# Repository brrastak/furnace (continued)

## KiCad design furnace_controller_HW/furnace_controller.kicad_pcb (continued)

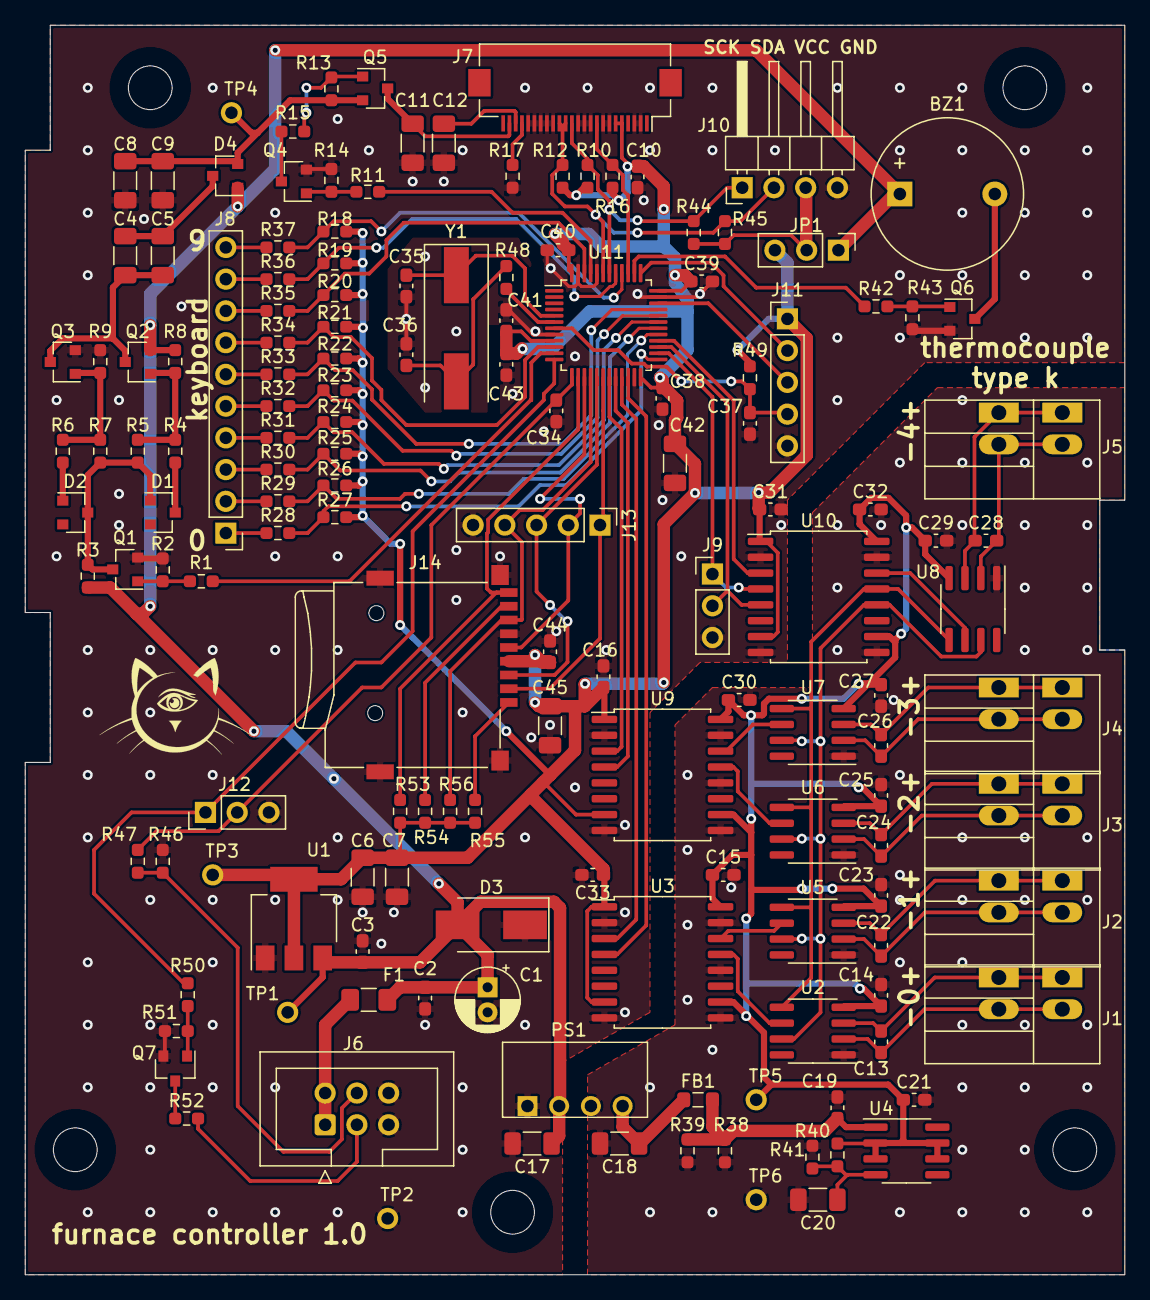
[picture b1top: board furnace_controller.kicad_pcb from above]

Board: 2 copper layers, 88.0 x 100.0 mm, 155 parts (0 on the bottom side), 96 nets.

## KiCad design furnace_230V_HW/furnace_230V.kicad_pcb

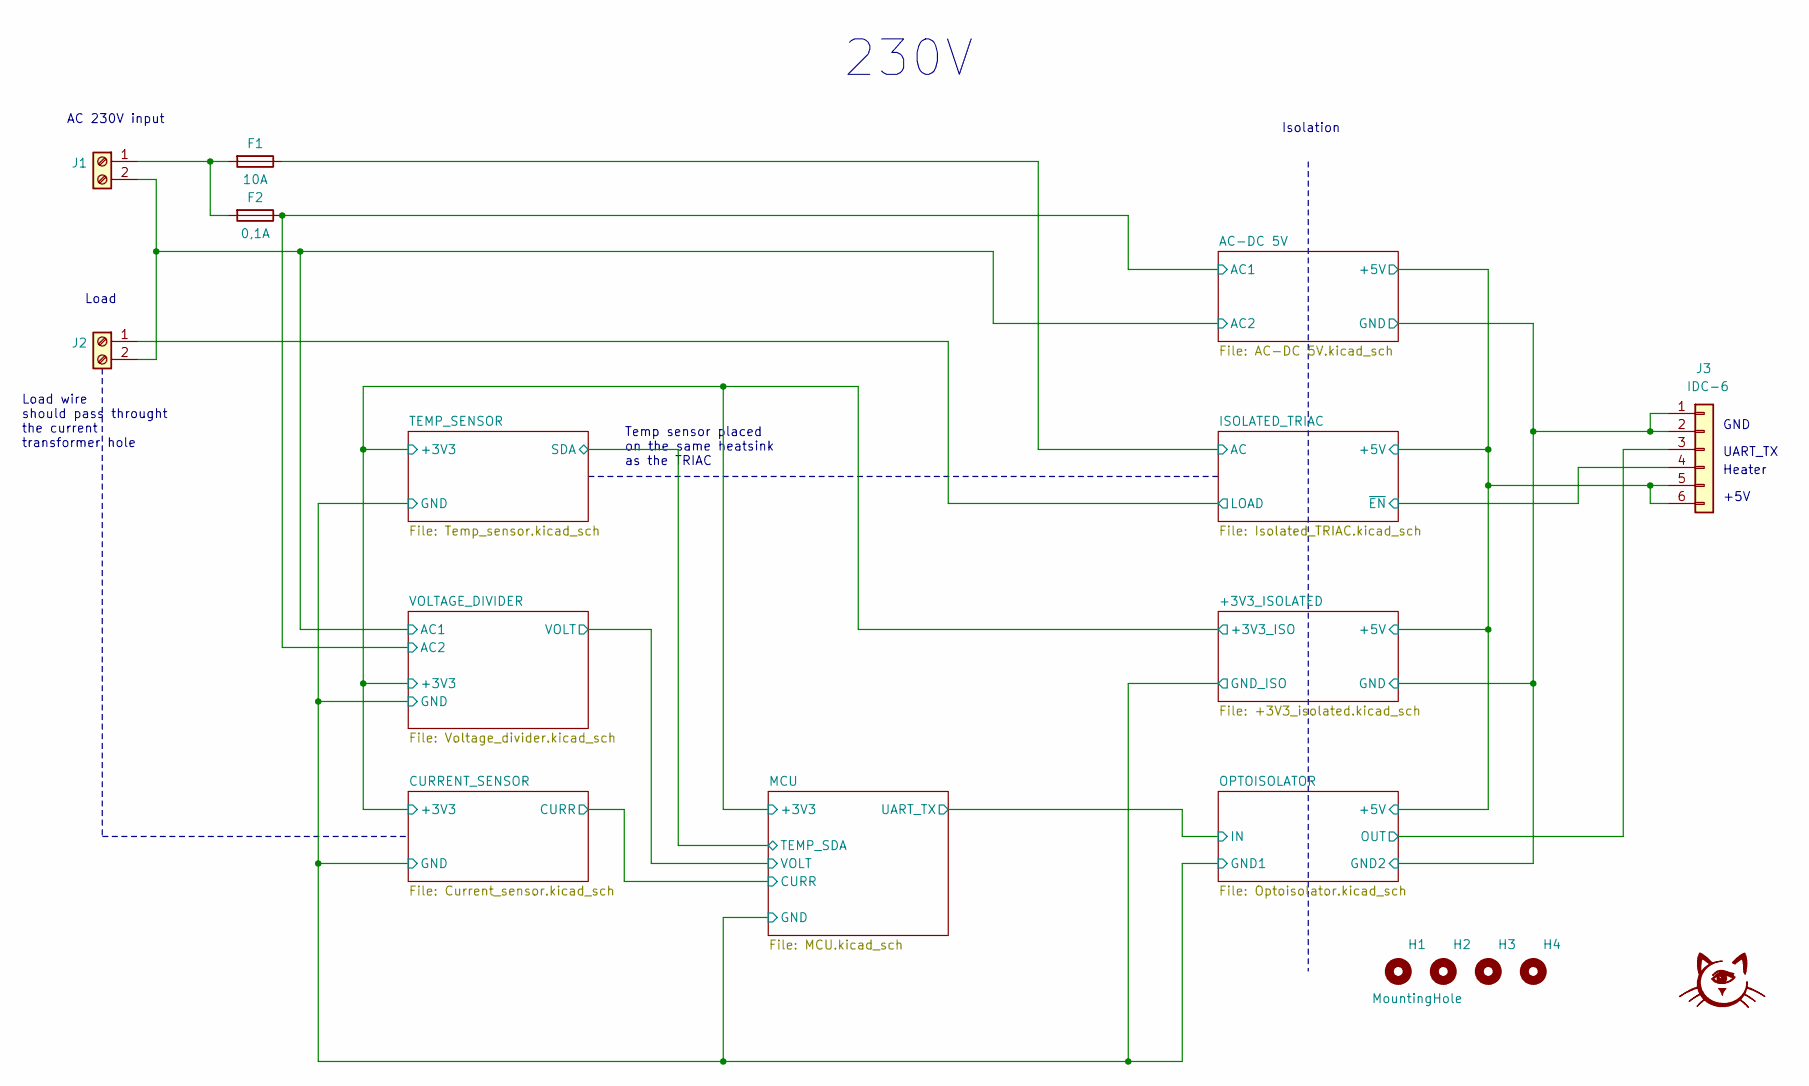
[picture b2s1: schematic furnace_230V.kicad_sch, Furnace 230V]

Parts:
F1: 10A; Fuseholder_Cylinder-5x20mm_Stelvio-Kontek_PTF78_Horizontal_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
F2: 0,1A; Fuseholder_Cylinder-5x20mm_Stelvio-Kontek_PTF78_Horizontal_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
G1: LOGO; stamp
H1, H2, H3, H4: MountingHole; hole_D3.5mm
J1, J2: KF7.62-2P
J3: IDC-6; IDC-Header_2x03_P2.54mm_Vertical

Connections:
/+3V3_ISOLATED/+5V: J3.5, J3.6; also elsewhere on the board
/+3V3_ISOLATED/GND: J3.1, J3.2; also elsewhere on the board
/AC-DC 5V/AC1: F2.1; also elsewhere on the board
/ISOLATED_TRIAC/AC: F1.1; also elsewhere on the board
/ISOLATED_TRIAC/LOAD: J2.1; also elsewhere on the board
/ISOLATED_TRIAC/~EN: J3.4; also elsewhere on the board
/OPTOISOLATOR/OUT: J3.3; also elsewhere on the board
/VOLTAGE_DIVIDER/AC1: J1.2, J2.2; also elsewhere on the board
unnamed: F1.2, F2.2, J1.1

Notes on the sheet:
GND
Isolation
230V
Load wire should pass throught the current transformer hole
AC 230V input
UART_TX
Load
Heater
Temp sensor placed on the same heatsink as the TRIAC
+5V

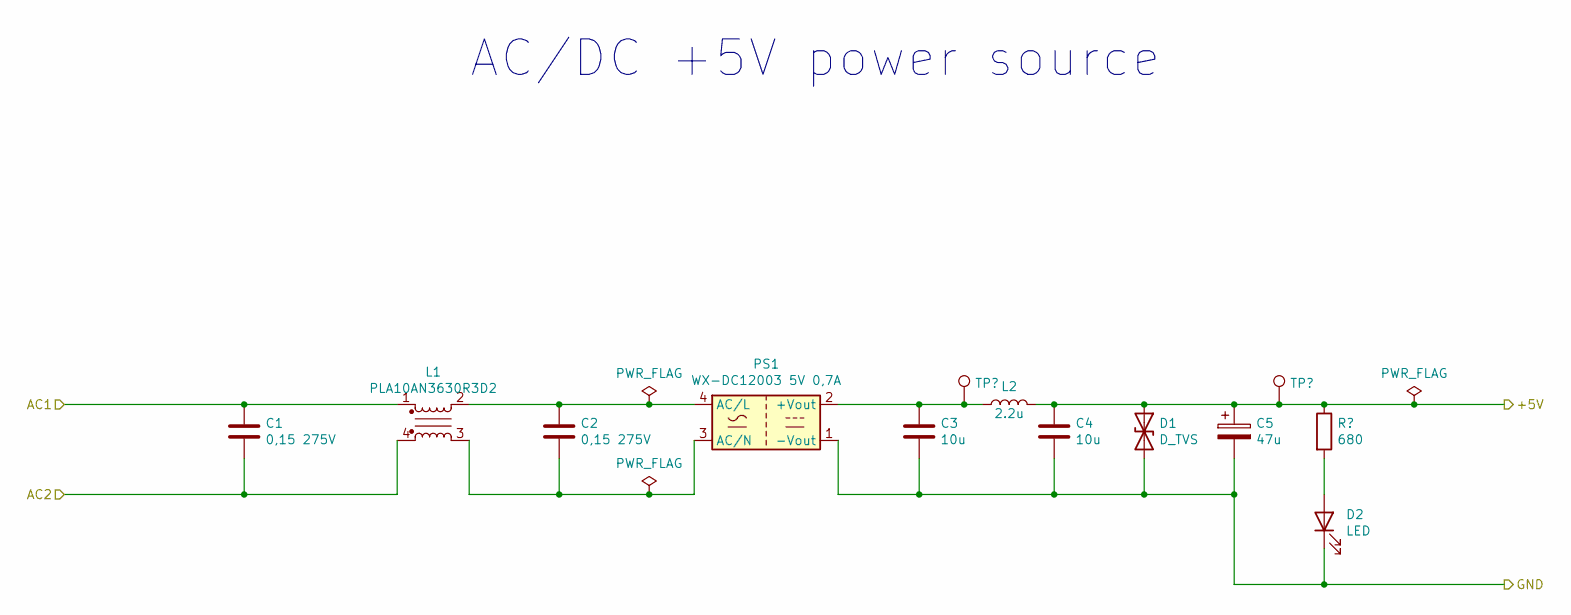
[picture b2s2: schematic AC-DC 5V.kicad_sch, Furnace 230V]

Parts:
C1, C2: 0,15 275V; C_Rect_L18.0mm_W7.0mm_P15.00mm_FKS3_FKP3
C3, C4: 10u; C_1206_3216Metric_Pad1.42x1.75mm_HandSolder
C5: 47u; CP_Radial_D5.0mm_P2.00mm
D1: D_TVS; D_SMB_Handsoldering
D2: LED; LED_1206_3216Metric_ReverseMount_Hole1.8x2.4mm
L1: PLA10AN3630R3D2; L_CommonMode_PLA10
L2: 2.2u; L_Axial_L7.0mm_D3.3mm_P10.16mm_Horizontal_Fastron_MICC
PS1: WX-DC12003 5V 0,7A; WX-DC12003
R1: 680; R_0603_1608Metric_Pad1.05x0.95mm_HandSolder
TP1, TP2: TestPoint; TP

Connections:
/+3V3_ISOLATED/+5V: C4.1, C5.1, D1.1 (A1), L2.2, R1.1, TP2.1; also elsewhere on the board
/+3V3_ISOLATED/GND: C3.2, C4.2, C5.2, D1.2 (A2), D2.1 (K), PS1.1 (-Vout); also elsewhere on the board
/AC-DC 5V/AC1: C1.1, L1.1; also elsewhere on the board
/VOLTAGE_DIVIDER/AC1: C1.2, L1.4; also elsewhere on the board
unnamed: C2.1, L1.2, PS1.4 (AC/L)
unnamed: C2.2, L1.3, PS1.3 (AC/N)
unnamed: C3.1, L2.1, PS1.2 (+Vout), TP1.1
unnamed: D2.2 (A), R1.2

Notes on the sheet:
AC/DC +5V power source

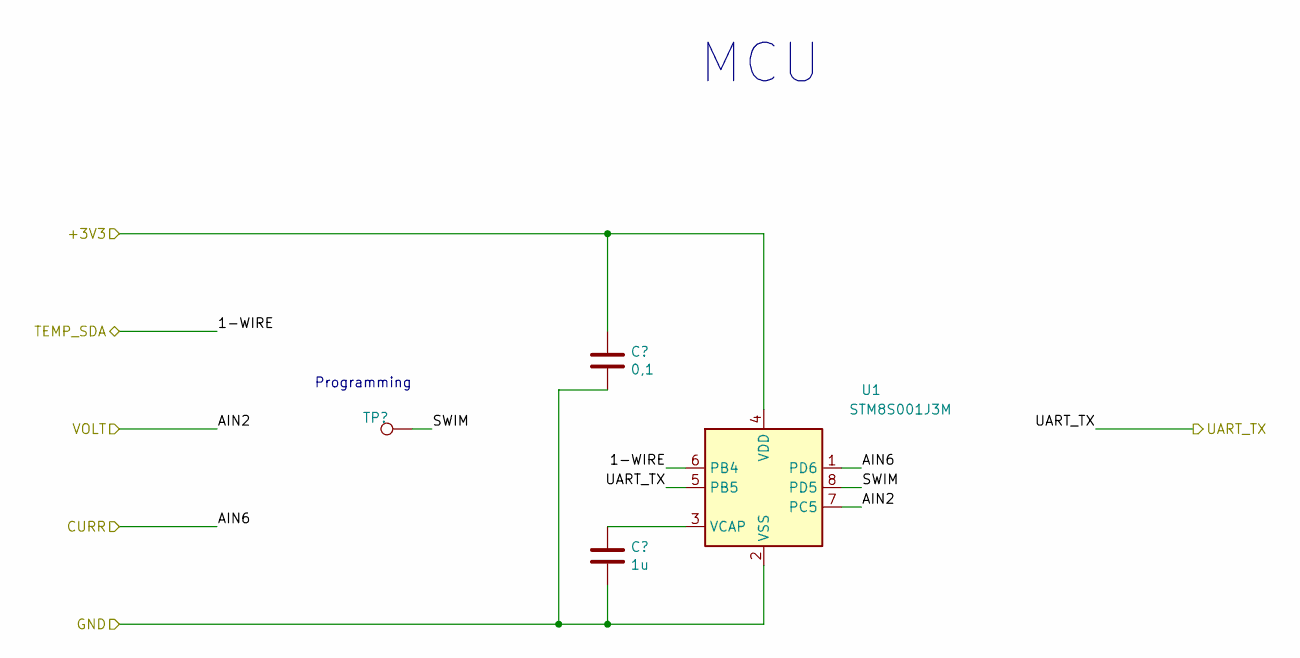
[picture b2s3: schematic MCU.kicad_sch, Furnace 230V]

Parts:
C6: 0,1; C_0603_1608Metric_Pad1.05x0.95mm_HandSolder
C7: 1u; C_0603_1608Metric_Pad1.05x0.95mm_HandSolder
TP3: TestPoint; TP
U1: STM8S001J3M; SOIC-8_3.9x4.9mm_P1.27mm

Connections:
/CURRENT_SENSOR/+3V3: C6.1, U1.4 (VDD); also elsewhere on the board
/CURRENT_SENSOR/CURR: U1.1 (PD6); also elsewhere on the board
/CURRENT_SENSOR/GND: C6.2, C7.2, U1.2 (VSS); also elsewhere on the board
/MCU/SWIM: TP3.1, U1.8 (PD5)
/MCU/VOLT: U1.7 (PC5); also elsewhere on the board
/OPTOISOLATOR/IN: U1.5 (PB5); also elsewhere on the board
/TEMP_SENSOR/SDA: U1.6 (PB4); also elsewhere on the board
unnamed: C7.1, U1.3 (VCAP)

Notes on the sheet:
MCU
Programming

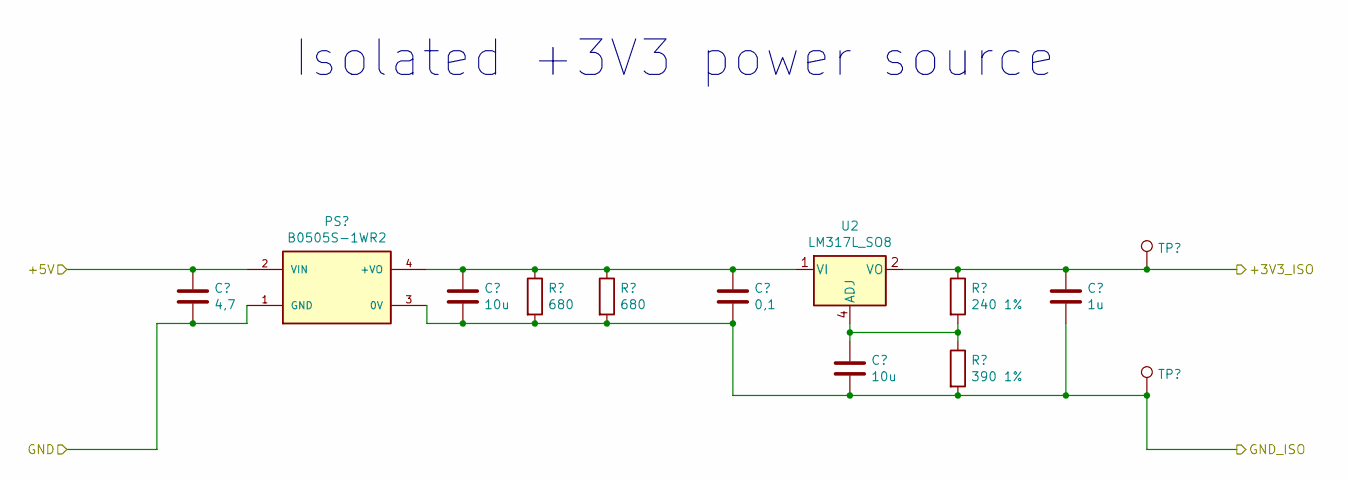
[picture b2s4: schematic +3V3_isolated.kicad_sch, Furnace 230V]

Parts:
C8: 4,7; C_1206_3216Metric_Pad1.42x1.75mm_HandSolder
C9, C11: 10u; C_1206_3216Metric_Pad1.42x1.75mm_HandSolder
C10: 0,1; C_0603_1608Metric_Pad1.05x0.95mm_HandSolder
C12: 1u; C_0603_1608Metric_Pad1.05x0.95mm_HandSolder
PS2: B0505S-1WR2; B_S-1WR3; PARTREV 2018.12.05-B/2
R2, R3: 680; R_0603_1608Metric_Pad1.05x0.95mm_HandSolder
R4: 240 1%; R_0603_1608Metric_Pad1.05x0.95mm_HandSolder
R5: 390 1%; R_0603_1608Metric_Pad1.05x0.95mm_HandSolder
TP4, TP5: TestPoint; TP
U2: LM317L_SO8; SOIC-8_3.9x4.9mm_P1.27mm

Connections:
/+3V3_ISOLATED/+5V: C8.1, PS2.2 (VIN); also elsewhere on the board
/+3V3_ISOLATED/GND: C8.2, PS2.1 (GND); also elsewhere on the board
/CURRENT_SENSOR/+3V3: C12.1, R4.1, TP4.1, U2.2 (VO), U2.3 (VO), U2.6 (VO), U2.7 (VO); also elsewhere on the board
/CURRENT_SENSOR/GND: C9.2, C10.2, C11.2, C12.2, PS2.3 (0V), R2.2, R3.2, R5.2, TP5.1; also elsewhere on the board
unnamed: C9.1, C10.1, PS2.4 (+VO), R2.1, R3.1, U2.1 (VI)
unnamed: C11.1, R4.2, R5.1, U2.4 (ADJ)

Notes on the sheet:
Isolated +3V3 power source

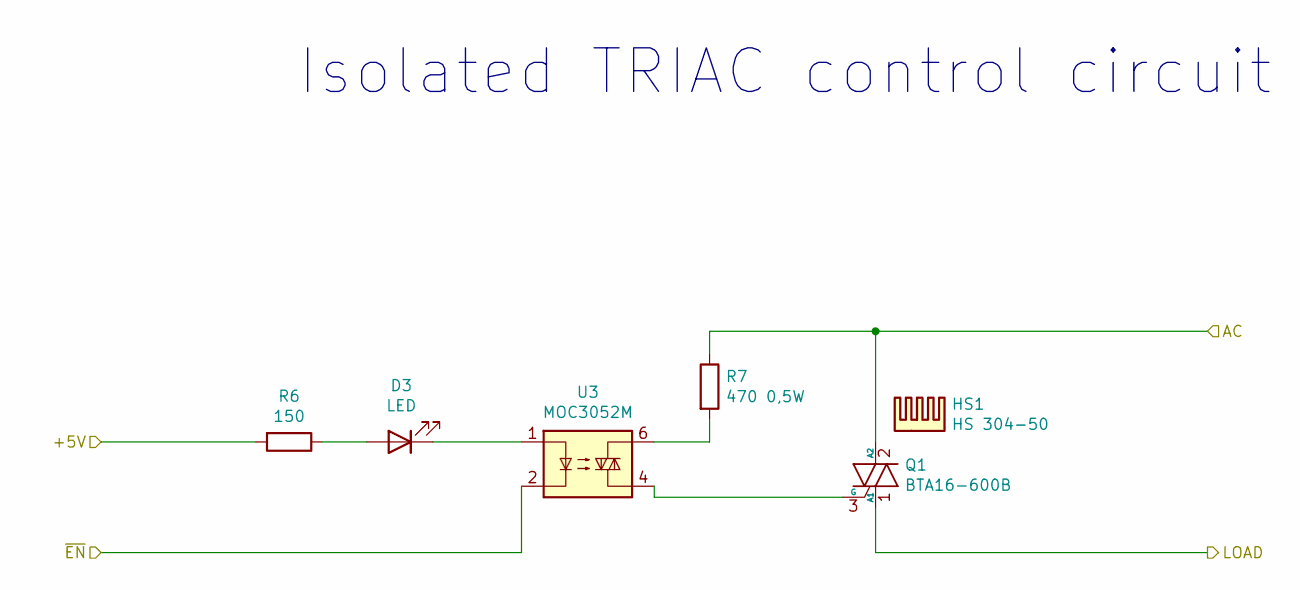
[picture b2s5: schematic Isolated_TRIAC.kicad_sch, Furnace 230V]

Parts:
D3: LED; LED_1206_3216Metric_ReverseMount_Hole1.8x2.4mm
HS1: HS 304-50; HS_304-50
Q1: BTA16-600B; TRIAC
R6: 150; R_0603_1608Metric_Pad1.05x0.95mm_HandSolder
R7: 470 0,5W; R_Axial_DIN0309_L9.0mm_D3.2mm_P12.70mm_Horizontal
U3: MOC3052M; DIP-6_W7.62mm_LongPads

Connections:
/+3V3_ISOLATED/+5V: R6.2; also elsewhere on the board
/ISOLATED_TRIAC/AC: Q1.2 (A2), R7.1; also elsewhere on the board
/ISOLATED_TRIAC/LOAD: Q1.1 (A1); also elsewhere on the board
/ISOLATED_TRIAC/~EN: U3.2; also elsewhere on the board
unnamed: D3.1 (K), U3.1
unnamed: D3.2 (A), R6.1
unnamed: Q1.3 (G), U3.4
unnamed: R7.2, U3.6

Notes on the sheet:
Isolated TRIAC control circuit

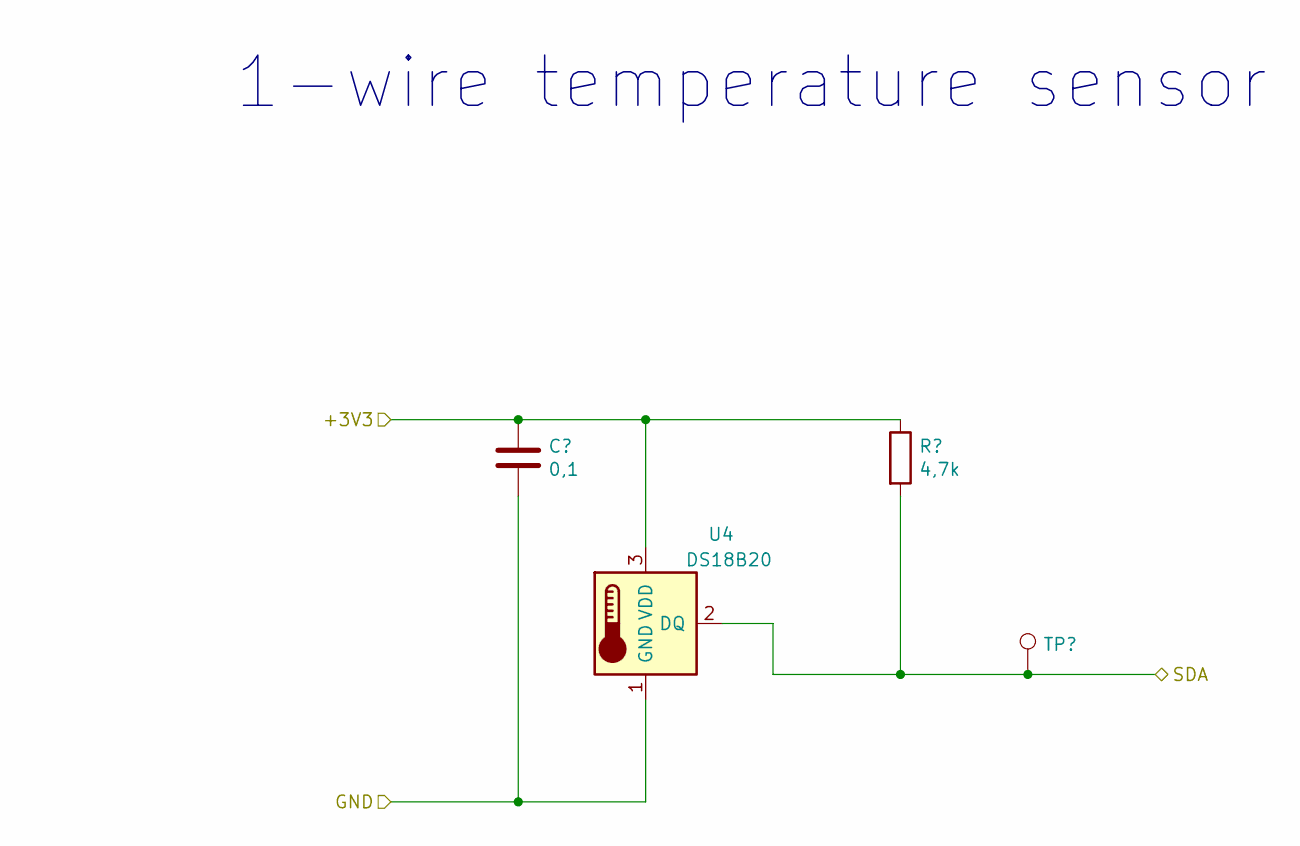
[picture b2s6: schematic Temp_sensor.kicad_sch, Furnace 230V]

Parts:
C13: 0,1; C_0603_1608Metric_Pad1.05x0.95mm_HandSolder
R8: 4,7k; R_0603_1608Metric_Pad1.05x0.95mm_HandSolder
TP6: TestPoint; TP
U4: DS18B20; TO-92_Inline

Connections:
/CURRENT_SENSOR/+3V3: C13.1, R8.1, U4.3 (VDD); also elsewhere on the board
/CURRENT_SENSOR/GND: C13.2, U4.1 (GND); also elsewhere on the board
/TEMP_SENSOR/SDA: R8.2, TP6.1, U4.2 (DQ); also elsewhere on the board

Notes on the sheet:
1-wire temperature sensor

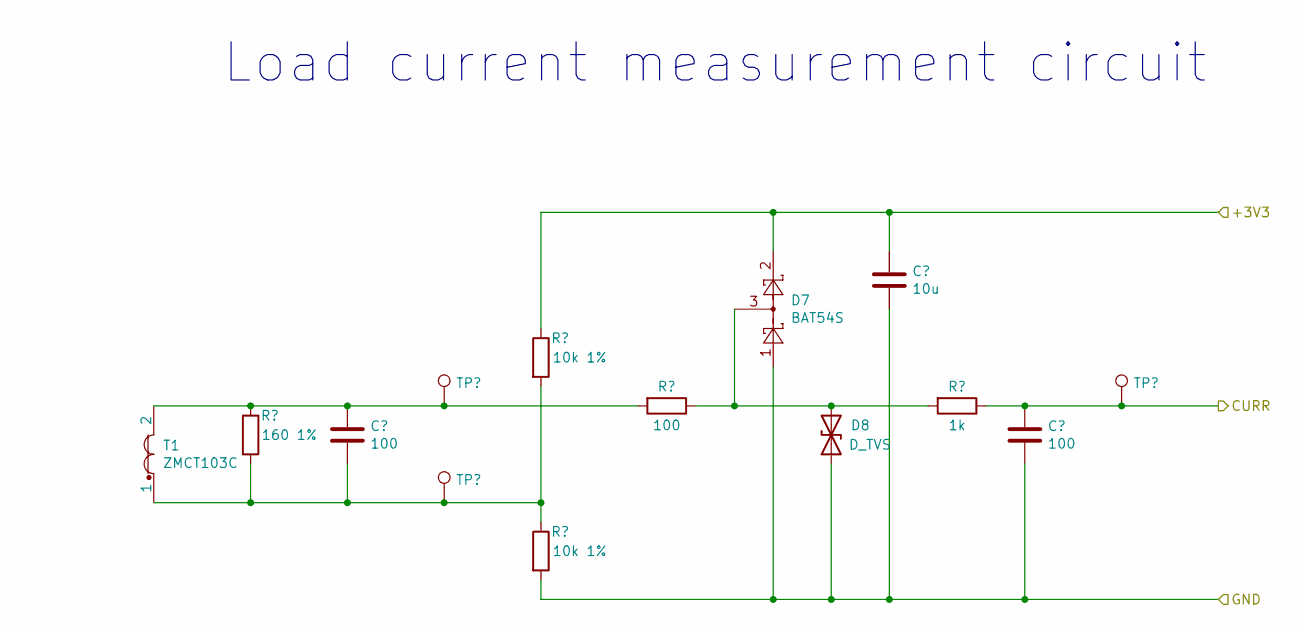
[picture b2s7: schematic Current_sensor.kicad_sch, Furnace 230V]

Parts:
C17, C19: 100; C_0603_1608Metric_Pad1.05x0.95mm_HandSolder
C18: 10u; C_0603_1608Metric_Pad1.05x0.95mm_HandSolder
D7: BAT54S; SOT-23
D8: D_TVS; D_SMB_Handsoldering
R16: 160 1%; R_0603_1608Metric_Pad1.05x0.95mm_HandSolder
R17, R18: 10k 1%; R_0603_1608Metric_Pad1.05x0.95mm_HandSolder
R19: 100; R_0603_1608Metric_Pad1.05x0.95mm_HandSolder
R20: 1k; R_0603_1608Metric_Pad1.05x0.95mm_HandSolder
T1: ZMCT103C
TP11, TP12, TP13: TestPoint; TP

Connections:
/CURRENT_SENSOR/+3V3: C18.1, D7.2, R17.1; also elsewhere on the board
/CURRENT_SENSOR/CURR: C19.1, R20.1, TP13.1; also elsewhere on the board
/CURRENT_SENSOR/GND: C18.2, C19.2, D7.1, D8.1 (A1), R18.2; also elsewhere on the board
unnamed: C17.1, R16.1, R19.2, T1.2, TP11.1
unnamed: C17.2, R16.2, R17.2, R18.1, T1.1, TP12.1
unnamed: D7.3, D8.2 (A2), R19.1, R20.2

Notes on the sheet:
Load current measurement circuit

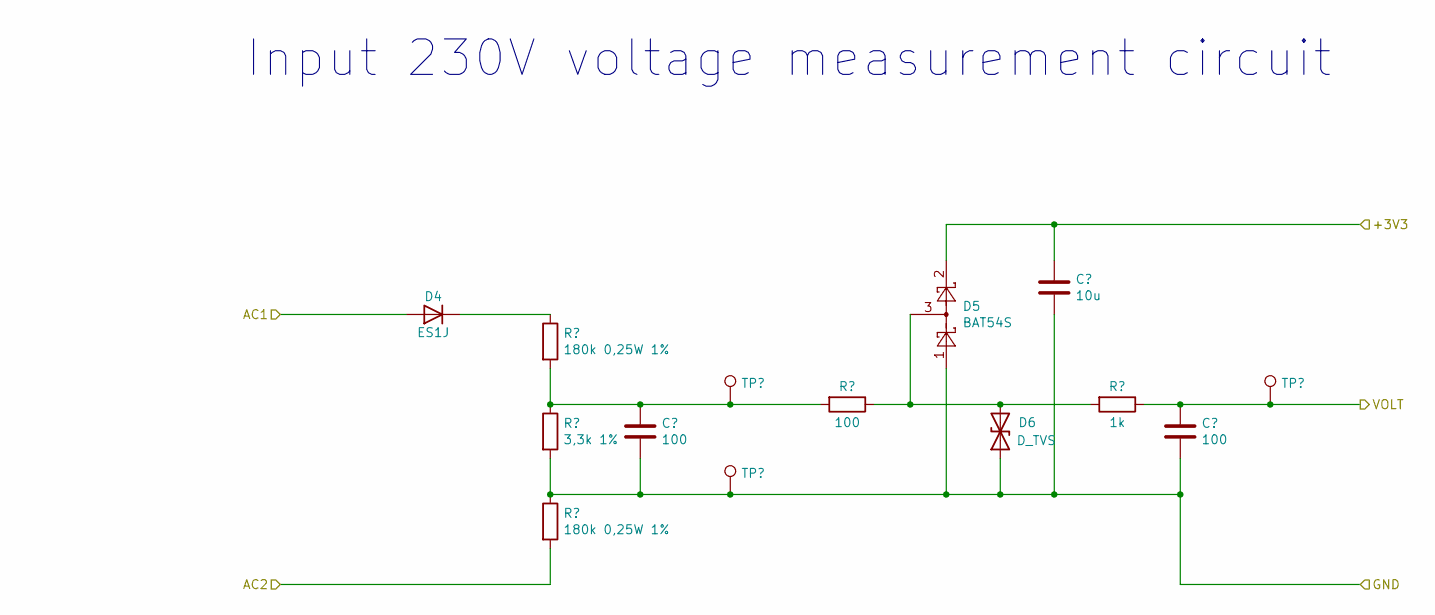
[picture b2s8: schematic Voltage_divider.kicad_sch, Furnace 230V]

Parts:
C14, C16: 100; C_0603_1608Metric_Pad1.05x0.95mm_HandSolder
C15: 10u; C_0603_1608Metric_Pad1.05x0.95mm_HandSolder
D4: ES1J; D_SMA_Handsoldering
D5: BAT54S; SOT-23
D6: D_TVS; D_SMB_Handsoldering
R9, R11: 180k 0,25W 1%; R_Axial_DIN0207_L6.3mm_D2.5mm_P10.16mm_Horizontal
R10: 3,3k 1%; R_0603_1608Metric_Pad1.05x0.95mm_HandSolder
R12: 100; R_0603_1608Metric_Pad1.05x0.95mm_HandSolder
R13: 1k; R_0603_1608Metric_Pad1.05x0.95mm_HandSolder
TP7, TP8, TP9: TestPoint; TP

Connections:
/AC-DC 5V/AC1: R11.2; also elsewhere on the board
/CURRENT_SENSOR/+3V3: C15.1, D5.2; also elsewhere on the board
/CURRENT_SENSOR/GND: C14.2, C15.2, C16.2, D5.1, D6.1 (A1), R10.2, R11.1, TP8.1; also elsewhere on the board
/MCU/VOLT: C16.1, R13.1, TP9.1; also elsewhere on the board
/VOLTAGE_DIVIDER/AC1: D4.2 (A); also elsewhere on the board
unnamed: C14.1, R9.2, R10.1, R12.2, TP7.1
unnamed: D4.1 (K), R9.1
unnamed: D5.3, D6.2 (A2), R12.1, R13.2

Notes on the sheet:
Input 230V voltage measurement circuit

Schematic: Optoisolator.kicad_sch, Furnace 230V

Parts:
R14: 680; R_0603_1608Metric_Pad1.05x0.95mm_HandSolder
R15: 3,3k; R_0603_1608Metric_Pad1.05x0.95mm_HandSolder
TP10: TestPoint; TP
U5: H11L1; DIP-6_W7.62mm_LongPads

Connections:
/+3V3_ISOLATED/+5V: R15.1, U5.6; also elsewhere on the board
/+3V3_ISOLATED/GND: U5.5; also elsewhere on the board
/CURRENT_SENSOR/GND: U5.2; also elsewhere on the board
/OPTOISOLATOR/IN: R14.2, TP10.1; also elsewhere on the board
/OPTOISOLATOR/OUT: R15.2, U5.4; also elsewhere on the board
unnamed: R14.1, U5.1

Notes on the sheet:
UART isolator

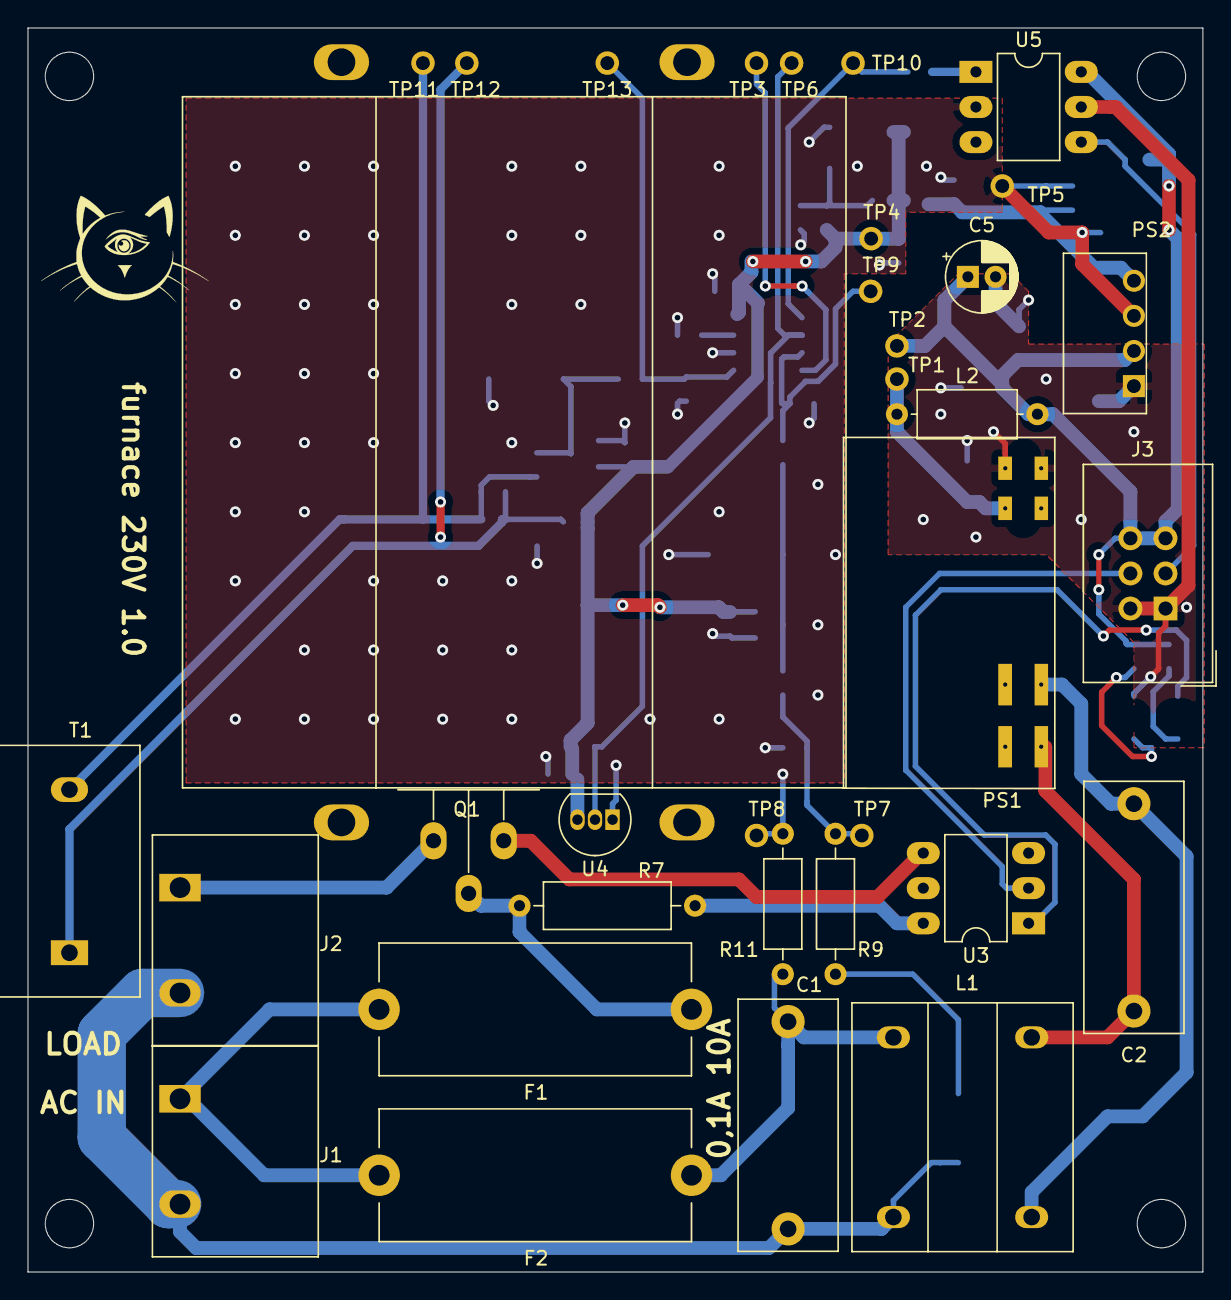
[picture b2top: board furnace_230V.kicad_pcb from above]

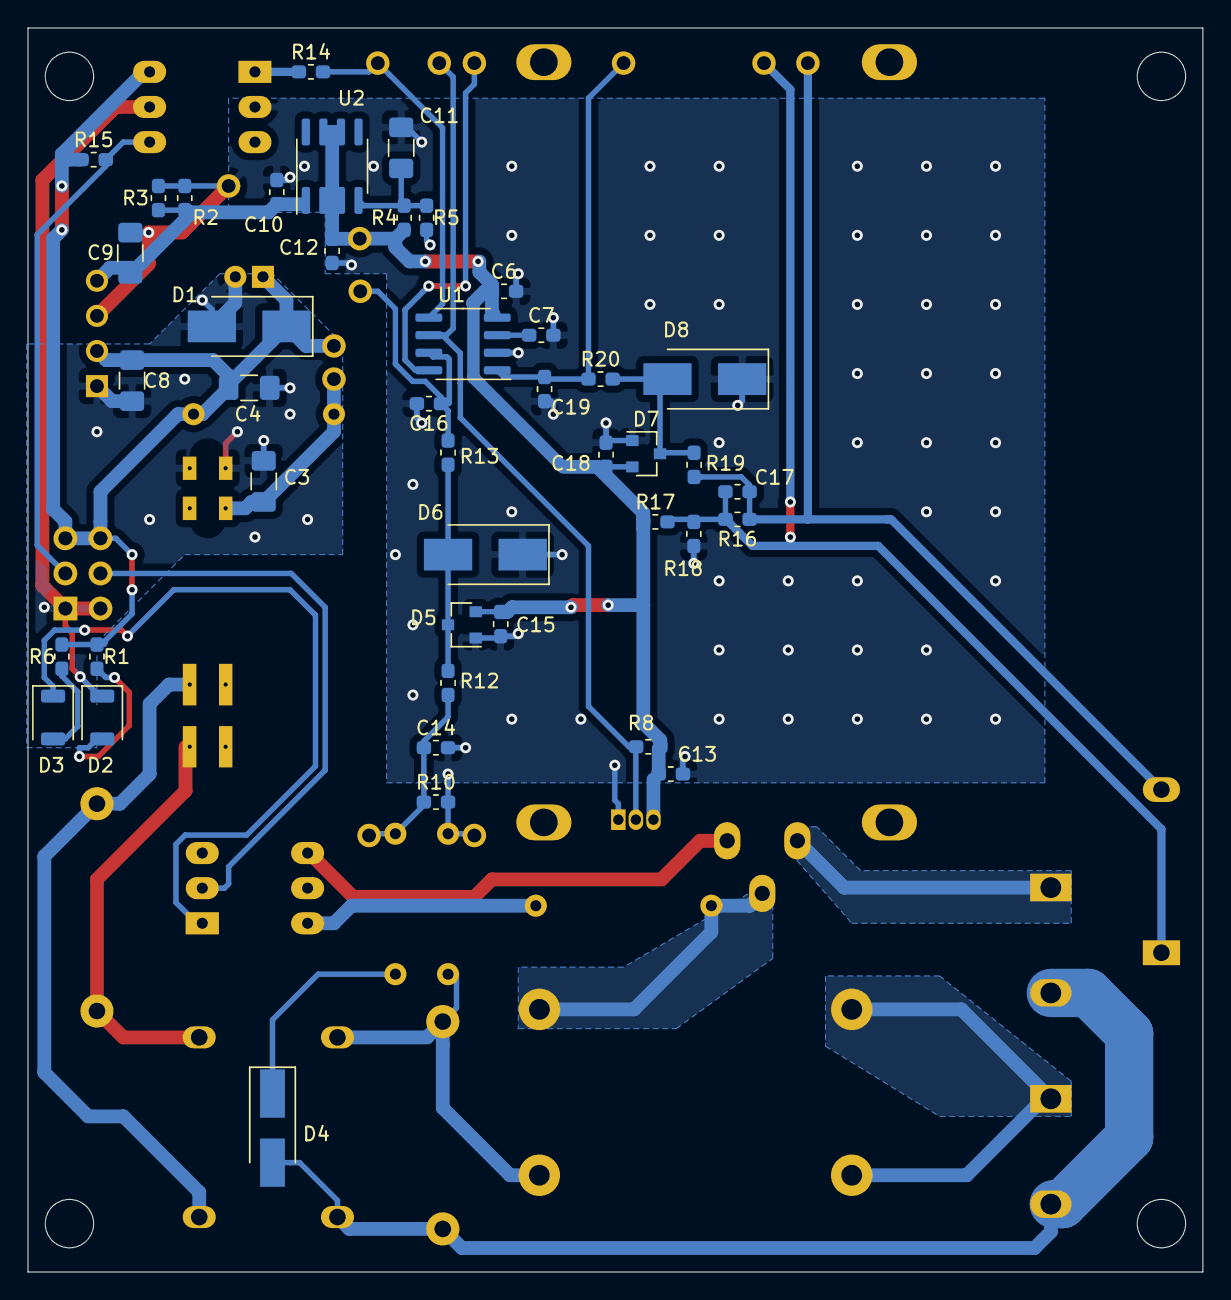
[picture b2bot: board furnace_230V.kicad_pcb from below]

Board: 2 copper layers, 85.0 x 90.0 mm, 82 parts (43 on the bottom side), 34 nets.

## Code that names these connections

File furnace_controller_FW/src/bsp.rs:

use display_interface_i2c::I2CInterface;
pub use stm32f1xx_hal as hal;
pub use hal:: {
        afio::spi2,
        prelude::*,
        rcc::*,
        gpio::*,
        i2c::{self, BlockingI2c, DutyCycle},
        pac::Peripherals,
        spi::{self, Spi, Phase, Polarity},
        time::ms,
        timer::{Channel, Timer, Tim2NoRemap},
        serial::{self, Rx},
        watchdog::IndependentWatchdog,
    };
pub use ssd1309::{prelude::*, Builder};

pub use crate::keyboard::*;
use crate::safe_panic::copy_safe_pin;


/// Number of thermocouples
pub const TEMP_NUM: usize = 5;
/// Number of bytes in each packet received from the 230V board
pub const RX_DATA_LEN: usize = 22;

/// Possible error while receiving the 230V board data
#[derive(Debug, PartialEq)]
pub enum Board230Error {
    UartError,
    CrcError,
    ParseError,
    NoTempValue,
}

/// Structure containing 230V board data
#[derive(Debug, PartialEq)]
pub struct RxData {
    /// RMS grid voltage value in V
    pub voltage: u16,
    /// RMS load current value in 0.1A
    pub current: u16,
    /// Triac temperature value in Celsius degree
    pub triac_temp: i16,
}


pub type OledDisplay = GraphicsMode<I2CInterface<BlockingI2c<hal::pac::I2C1>>>;
pub type DigitalOutput = ErasedPin<Output>;
pub type TempSpi = Spi<hal::pac::SPI2, u8, PullUp>;
pub type Board230Rx = Rx<hal::pac::USART2>;

pub struct Board {
    pub rcc: Rcc,
    pub oled: OledDisplay,
    pub heater_control: &'static mut DigitalOutput,
    pub buzzer: DigitalOutput,
    pub keyboard: Keyboard,
    pub watchdog: IndependentWatchdog,
    pub temp_select: [DigitalOutput; 5],
    pub temp_spi: TempSpi,
    pub board230_rx: Board230Rx,
}

impl Board {

    pub fn new(p: Peripherals) -> Self {

        let mut flash = p.FLASH.constrain();
        let mut rcc = p.RCC.freeze(
            Config::hse(8.MHz()).sysclk(72.MHz()).pclk1(36.MHz()).pclk2(72.MHz()),
            &mut flash.acr,
        );
        let mut afio = p.AFIO.constrain(&mut rcc);

        let mut gpioa = p.GPIOA.split(&mut rcc);
        let mut gpiob = p.GPIOB.split(&mut rcc);

        let (pa15, pb3, pb4) = afio.mapr.disable_jtag(gpioa.pa15, gpiob.pb3, gpiob.pb4);

        // Discrete outputs
        let heater_control = copy_safe_pin(
            gpioa.pa2.into_push_pull_output_with_state(&mut gpioa.crl, PinState::Low).erase()
        );
        let mut display_power_en = gpiob.pb8.into_push_pull_output(&mut gpiob.crh).erase();
        let buzzer = pa15.into_push_pull_output_with_state(&mut gpioa.crh, PinState::Low).erase();

        // Keyboard
        let keyboard_rows = [
            gpioa.pa8.into_floating_input(&mut gpioa.crh).erase(),
            gpioa.pa9.into_floating_input(&mut gpioa.crh).erase(),
            gpioa.pa10.into_floating_input(&mut gpioa.crh).erase(),
            gpioa.pa11.into_floating_input(&mut gpioa.crh).erase(),
            gpioa.pa12.into_floating_input(&mut gpioa.crh).erase(),
        ];
        let keyboard_cols = [
            pb4.into_open_drain_output_with_state(&mut gpiob.crl, PinState::High).erase(),
            gpiob.pb5.into_open_drain_output_with_state(&mut gpiob.crl, PinState::High).erase(),
            gpiob.pb9.into_open_drain_output_with_state(&mut gpiob.crh, PinState::High).erase(),
            gpioa.pa0.into_open_drain_output_with_state(&mut gpioa.crl, PinState::High).erase(),
        ];
        let keyboard = Keyboard::new(keyboard_rows, keyboard_cols);

        // Charge pump clock
        let charge_pump_clk = gpioa.pa1.into_alternate_push_pull(&mut gpioa.crl);
        let mut pwm = p.TIM2
            .pwm_hz::<Tim2NoRemap, _, _>(charge_pump_clk, &mut afio.mapr, 10.kHz(), &mut rcc);
        pwm.enable(Channel::C2);
        pwm.set_duty(Channel::C2, pwm.get_max_duty() / 3);

        // OLED display
        let mut display_reset = pb3.into_push_pull_output(&mut gpiob.crl);
        let display_i2c_clk = gpiob.pb6.into_alternate_open_drain(&mut gpiob.crl);
        let display_i2c_sda = gpiob.pb7.into_alternate_open_drain(&mut gpiob.crl);
        display_power_en.set_high();
        let mut display_delay = p.TIM4.delay_us(&mut rcc);
        let display_i2c = BlockingI2c::new(
            p.I2C1,
            (display_i2c_clk, display_i2c_sda),
            i2c::Mode::Fast {
                frequency: 100u32.kHz(),
                duty_cycle: DutyCycle::Ratio2to1,
            },
            &mut rcc,
            1000,
            10,
            1000,
            1000,
        );
        let i2c_interface = I2CInterface::new(display_i2c, 0x3C, 0x40);
        let mut oled: GraphicsMode<_> = Builder::new()
            .with_rotation(DisplayRotation::Rotate180)
            .connect(i2c_interface)
            .into();
        oled.reset(&mut display_reset, &mut display_delay).unwrap();

        // SPI for thermocouples
        let temp_spi_cs0 = gpiob.pb10.into_push_pull_output_with_state(&mut gpiob.crh, PinState::High).erase();
        let temp_spi_cs1 = gpiob.pb11.into_push_pull_output_with_state(&mut gpiob.crh, PinState::High).erase();
        let temp_spi_cs2 = gpiob.pb1.into_push_pull_output_with_state(&mut gpiob.crl, PinState::High).erase();
        let temp_spi_cs3 = gpiob.pb2.into_push_pull_output_with_state(&mut gpiob.crl, PinState::High).erase();
        let temp_spi_cs4 = gpiob.pb15.into_push_pull_output_with_state(&mut gpiob.crh, PinState::High).erase();
        let temp_select = [temp_spi_cs0, temp_spi_cs1, temp_spi_cs2, temp_spi_cs3, temp_spi_cs4];
        assert_eq!(temp_select.len(), TEMP_NUM);
        let temp_spi_clk = gpiob.pb13.into_alternate_push_pull(&mut gpiob.crh);
        let temp_spi_miso = gpiob.pb14.into_pull_up_input(&mut gpiob.crh);
        let temp_spi = Spi::new(
            p.SPI2,
            (Some(temp_spi_clk), Some(temp_spi_miso), None::<spi2::Mo>),
            spi::Mode{polarity: Polarity::IdleLow, phase: Phase::CaptureOnFirstTransition},
            2.MHz(),
            &mut rcc
        );

        // UART to receive data from the 230V board
        let rx_pin = gpioa.pa3.into_floating_input(&mut gpioa.crl);
        let board230_rx = p.USART2.rx(
            rx_pin,
            serial::Config::default()
                .baudrate(9600.bps())
                .wordlength_8bits()
                .parity_none()
                .stopbits(serial::StopBits::STOP1),
            &mut rcc
        );

        let mut watchdog = IndependentWatchdog::new(p.IWDG);
        watchdog.start(3000.millis());


        Board {
            rcc,
            oled,
            heater_control,
            buzzer,
            keyboard,
            watchdog,
            temp_select,
            temp_spi,
            board230_rx,
        }
    }
}

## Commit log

2021-05-13 Create empty
2024-12-05 Change directories structure
2024-12-06 Resave in KiCad 8
2024-12-06 Add README
2024-12-16 Add licence
2025-03-27 Add charge pump simulation
2025-03-29 Tune FETs switchng times and frequency
2025-04-03 Update embed settings format
2025-04-12 Add ADC values proceeding
2025-04-12 Add i32_load16_s()
2025-04-12 Add sensor ds18b20
2025-04-12 Add board support package
2025-04-12 Add i32_load16_u(), REM_U()
2025-04-12 Add CRC8
2025-04-15 Change directory structure
2025-04-15 Add digital filter simulation
2025-04-15 Add digital filter
2025-04-16 Add temperature sensor error handling
2025-04-16 Check CRC8 algorithms
2025-04-17 Replace CRC8 implementation
2025-04-26 Fill README
2026-01-04 Add buzzer and keyboard
2026-01-04 Add watchdog
2026-01-04 Add safe panic
2026-01-04 Add thermocouples
2026-01-08 Fix the 230V board UART input
2026-01-08 Resave in Kicad 9
2026-01-08 Tune resistor values for the proper charge pump MOSFETs deadtime
2026-01-08 Make error[E0463]: can't find crate for `test` less annoying
2026-01-09 Add reading data from the 230V board
2026-03-08 Add controller board enclosure
2026-03-08 Finalize enclosure
2026-06-16 Add logging
2026-06-17 Fix option bytes
2026-06-18 Add thermocouple data pin pull-up
